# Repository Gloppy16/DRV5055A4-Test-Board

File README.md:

# DRV5055A4-Test-Board
DRV5055A4 Test Board

Currently under developemnt. Use with caution.

If a low pass filter is added, you must cut the JP1 Jumper. Removing the jumper from the design will also work.

5 boards are $20 assembled (Without headers) from JLCPCB.

The following render has the low pass filter in place. If the boards are made from the fabrication files, the low pass components (R1 and C1) will not be populated.

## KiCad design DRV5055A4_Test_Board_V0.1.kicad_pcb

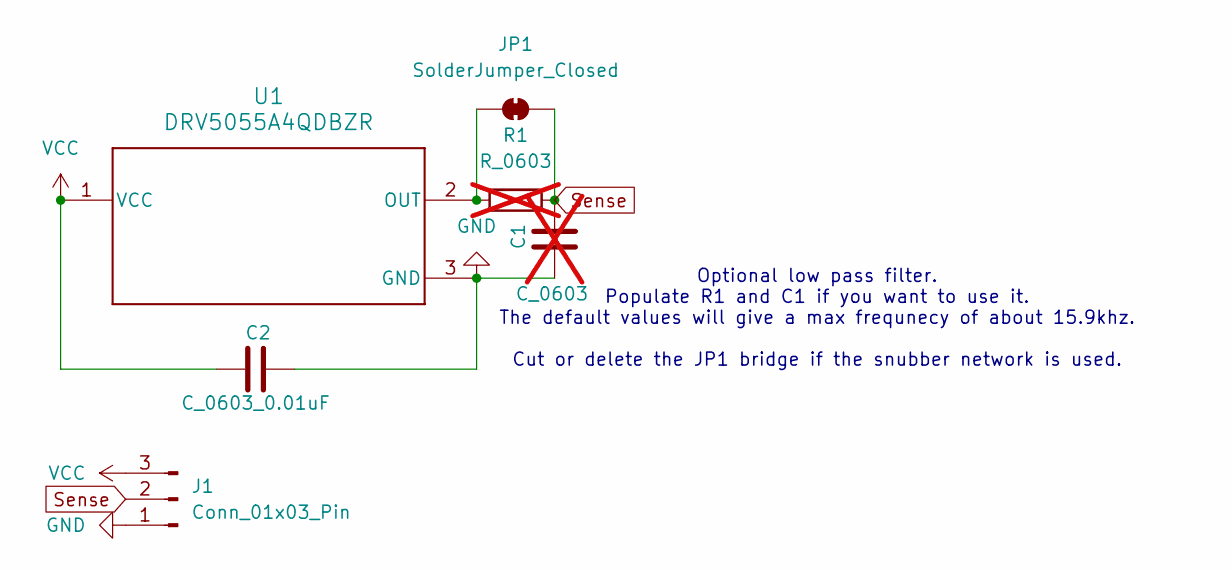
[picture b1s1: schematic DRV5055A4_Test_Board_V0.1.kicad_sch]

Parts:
C1: C_0603; C_0603_1608Metric_Pad1.08x0.95mm_HandSolder; JLCPCB Part Number C57112; not fitted
C2: C_0603_0.01uF; C_0603_1608Metric; JLCPCB Part Number C57112
J1: Conn_01x03_Pin; PinHeader_1x03_P2.54mm_Vertical
JP1: SolderJumper_Closed; SolderJumper-2_P1.3mm_Bridged_RoundedPad1.0x1.5mm
R1: R_0603; R_0603_1608Metric_Pad0.98x0.95mm_HandSolder; JLCPCB Part Number C21190; not fitted
U1: DRV5055A4QDBZR; DBZ0003A_N; JLCPCB Part Number C266123

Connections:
GND: C1.1, C2.2, J1.1, U1.3 (GND)
unnamed: JP1.1 (A), R1.1, U1.2 (OUT)
Sense: C1.2, J1.2, JP1.2 (B), R1.2
VCC: C2.1, J1.3, U1.1 (VCC)

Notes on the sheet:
Optional low pass filter. Populate R1 and C1 if you want to use it. The default values will give a max frequnecy of about 15.9khz. Cut or delete the JP1 bridge if the snubber network is used.

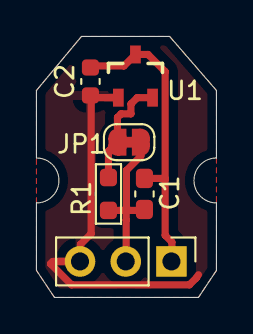
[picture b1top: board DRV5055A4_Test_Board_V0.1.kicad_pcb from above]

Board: 2 copper layers, 10.0 x 14.5 mm, 6 parts (0 on the bottom side), 4 nets.

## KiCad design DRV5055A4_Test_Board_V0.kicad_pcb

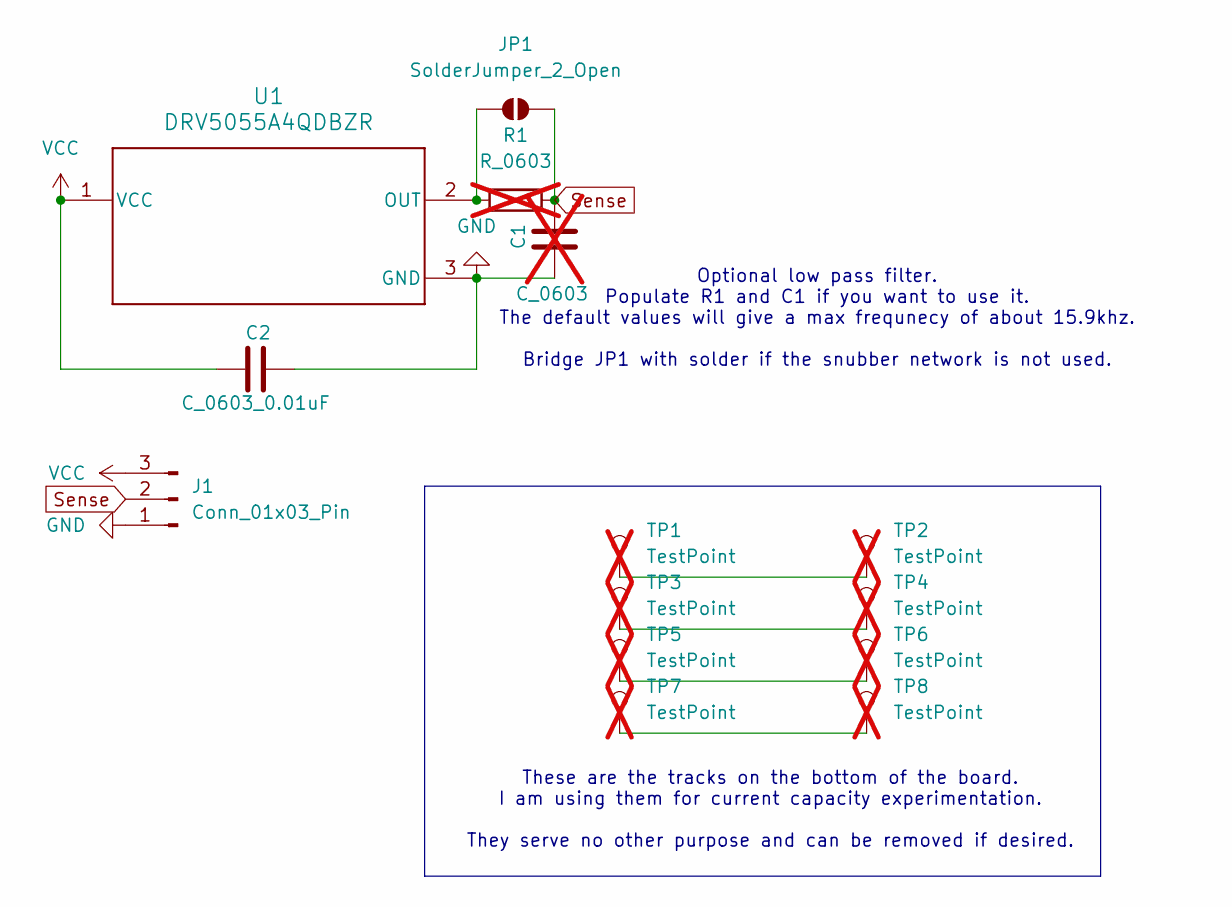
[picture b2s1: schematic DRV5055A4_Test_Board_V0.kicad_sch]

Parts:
C1: C_0603; C_0603_1608Metric_Pad1.08x0.95mm_HandSolder; JLCPCB Part Number C57112; not fitted
C2: C_0603_0.01uF; C_0603_1608Metric_Pad1.08x0.95mm_HandSolder; JLCPCB Part Number C57112
J1: Conn_01x03_Pin; PinHeader_1x03_P2.54mm_Vertical
JP1: SolderJumper_2_Open; SolderJumper-2_P1.3mm_Open_RoundedPad1.0x1.5mm
R1: R_0603; R_0603_1608Metric_Pad0.98x0.95mm_HandSolder; JLCPCB Part Number C21190; not fitted
TP1, TP2, TP3, TP4, TP5, TP6, TP7, TP8: TestPoint; TestPoint_THTPad_D1.0mm_Drill0.5mm_No_Silkscreen; not fitted
U1: DRV5055A4QDBZR; DBZ0003A_N; JLCPCB Part Number C266123

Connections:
GND: C1.1, C2.2, J1.1, U1.3 (GND)
unnamed: JP1.1 (A), R1.1, U1.2 (OUT)
unnamed: TP1.1, TP2.1
unnamed: TP3.1, TP4.1
unnamed: TP5.1, TP6.1
unnamed: TP7.1, TP8.1
Sense: C1.2, J1.2, JP1.2 (B), R1.2
VCC: C2.1, J1.3, U1.1 (VCC)

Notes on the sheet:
These are the tracks on the bottom of the board. I am using them for current capacity experimentation. They serve no other purpose and can be removed if desired.
Optional low pass filter. Populate R1 and C1 if you want to use it. The default values will give a max frequnecy of about 15.9khz. Bridge JP1 with solder if the snubber network is not used.

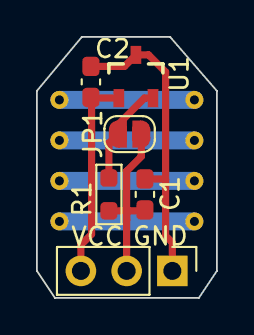
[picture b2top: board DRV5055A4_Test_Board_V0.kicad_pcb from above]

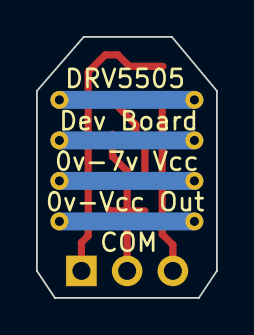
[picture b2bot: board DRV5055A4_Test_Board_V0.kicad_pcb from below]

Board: 2 copper layers, 10.0 x 14.5 mm, 14 parts (8 on the bottom side), 8 nets.

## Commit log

2024-08-03 Added Files
2024-08-04 Update README.md
    Removed random word
2024-08-04 Update README.md
    Added image and description of image
